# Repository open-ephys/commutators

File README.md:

> [!Important]  
> This repository has been split into dedicated repositories for each design:
>
>  - https://github.com/open-ephys/commutator-coax
>  - https://github.com/open-ephys/commutator-spi
>  - https://github.com/open-ephys/commutator-dual
>  - etc.
>
> Future commutator designs, issue tracking, etc. will take place in those repositories.
> This repository is deprecated.

# Torque-free commutators for orientation-aware headstages and miniscopes
The wide-spread availability of 6 degree of freedom pose tracking using
internal-measurement units (IMUs) allows continuous monitoring of an animal's
rotational state in an environment. This obviates the need for tether torque
measurements to drive an active commutator since the rotational state of the
animal is known in real-time, and the commutator can simply follow along. This
permits the use of extremely thin [coaxial
tethers](http://www.axon-cable.com/en/02_products/06_coaxial-cables/02/index.aspx)
that cannot function with a standard active commutator because they are too
flexible to translate rotational torque.

This commutator functions with headstages and miniscopes that provide
provide appropriate rotational tracking information. Currently
supported devices are next-generation, serialized headstages and miniscopes
such as [ONIX headstages](https://open-ephys.github.io/onix-docs/index.html), 
and UCLA Miniscope 4.0, and Open Ephys 3D low-profile SPI headstages.
However, this device operations completely independently from the headstage
itself, so can be used with any device that provides accurate, drift-free
rotational state. It can even be used without an IMU, e.g. using video-based
rotation tracking since its remote control interface is agnostic to how
rotational measurements are taken.

## Features
- Variants for high bandwidth RF links up to 18 GHz and low-bandwidth SPI cables
- Optical table & 80/20 rail mountable
- Remote control using JSON-encoded commands
- Manual control using capacitive sense buttons
- Indication LED
    - Can be completely turned off
- Advanced stepper driver (TMC2130)
    - Voltage-controlled for silent operation
    - Precise motion using step interpolation (256 uSteps/step)
- USB powered and controlled
    - Internal super-capacitor circuitry prevents loading the USB bus during
      motion

## Usage

**Note**: A high-quality, within-spec micro USB cable must be used when connecting 
the commutator to the host computer.

### LED
The LED tells you about the commutator state:

1. Flashing red (*Charging*): commutator is charging internal super-capacitors.
   All controls and motor operation are locked. Wait until this process
   completes to use the device. It can take up to 30 seconds.
1. Solid red (*Disabled*): commutator is disabled. Motor is turned off and will not
   turn or respond to button presses or external commands.
1. Green (*Enabled*): commutator is enabled and permits both remote and manual
   (button) turn control. Buttons take precedence over remote commands.

### Buttons
The front panel has four buttons.

- __Enable/Disable__: toggle commutator enable/disable.
    - *Disabled* (LED is red): All motor output will halt instantly, and motor
      driver is powered down. Pressing directional buttons in the stopped state
      will not work. All target turns provided via remote calls will be
      cleared, such that re-enable the motor will not result in the commutator
      re-engaging an old target position. In this state, pressing 
      the Enable/Disable button, or sending the approriate remote
      command, will enable the device.
    - *Enabled* (LED  green): When in the *enabled* state, the LED will be
      green and the motor can be turned via button presses or RPCs . In this
      state, pressing the Stop/Go button, or sending the approriate remote
      command, will instantly disable the device.

- __Directional__ (2x): Manually control the motor rotation in the
  direction indicated on each button when the commutator is *Enabled*. These
  inputs take precedence over and override ongoing remote motor control.  When
  pressed, all target turns provided via remote control will be cleared, such
  that releasing them will not result in the commutator re-engaging an old
  target position. Remote commands sent when a button is being pressed are
  ignored.

- __LED__: pressing the LED will toggled on and off (e.g for cases where it presents an
  unwanted visual stimulus).

### Remote control interface
When manual buttons are not being pressed, the commutator accepts JSON-encoded
commands over its serial interface. Here are examples of all commands that can
be sent:
```
{enable : true}     // Enable commutator (default = false)
{led : false}       // Turn off RGB LED (default = true)
{speed : 250}       // Set turn speed to 250 RPM (default = 50 RPM, valid ∈ (0, 500] RPM)
{turn : 1.1}        // 1.1 turns CW
{turn : -1.1}       // 1.1 turns CCW

// Example multi-command. Any combo can be used.
// In this case:
// 1. Turn LED off
// 1. Set speed to 25 RPM
// 2. Excecute 1.1 turns CC
// Ordering of commands does not matter, it is determined by the firmware
{led: false, speed: 25, turn : -1.1}
```
The communator state can be read using the `{print:}` command  which will
return a JSON object containing version, state, and motor parameters.

### Saving settings
All control and speed parameters, whether changed via the remote or manual
interface, are saved in non-volatile memory each time they are changed. The
device will start in the same state it was last used.

## Firmware
The controller firmware is located [here](./firmware/commutator). It runs on a
[Teensy lc](https://www.pjrc.com/store/teensylc.html). To compile
this firmware and program the microcontroller, you need the following
dependencies:

- [Arduino IDE](https://www.arduino.cc/en/Main/Software)
- [Teensyduino add-on](https://www.pjrc.com/teensy/td_download.html)
- [AccelStepper](https://www.airspayce.com/mikem/arduino/AccelStepper/)
- [Arduino JSON](https://arduinojson.org/)

The firmware can be uploaded to the device using the [Arduino
IDE](https://www.arduino.cc/en/Main/Software). _Note that you will need to add
the [Teensyduino add-on](https://www.pjrc.com/teensy/teensyduino.html) to to
the Arduino IDE to program the Teensy_. When installing Teensyduino, you should
opt to install all of the bundled libraries as well. This takes care of
installing `AccelStepper` library rather than having to install it manually.
ArduinoJSON can be installed through the Arduino IDE's package manager.

## Construction

### Bill of Materials
The BOM is located [here](https://docs.google.com/spreadsheets/d/1M2R0Q2-OuRHzctt05BxtA3hxNcCHtRZHORzCKElmG1Q/edit#gid=1283420334).

### Mechanical
The mechanical component of the commutator are as follows:

1. RF Rotary Joint
1. 2x reduction gears (3D-printed)
1. NEMA-11 Stepper Motor
1. Housing (3D-printed)
1. Some fasteners

Mechanical designs are located [here](./mechanical/). STL files for 3D printing
are located in the `stl` subdirectory. Links to purchase each of these
components, including 3D-printed parts, can be found on the BOM.

### Electronics
The board used to control the commutator consists of the following elements:

1. [Teensy LC](https://www.pjrc.com/store/teensylc.html) for receiving
   commands and controlling all circuit elements.
1. [TMC2130 stepper driver](https://www.analog.com/media/en/technical-documentation/data-sheets/TMC2130_datasheet_rev1.15.pdf) for driving the
   motor.
1. Super-capacitor charge system and step-up regulator for providing
   high-current capacity drive to the motor driver directly from USB.
1. RGB indicator LED.
1. Capacitive touch sensors on the back side of the PCB that serve as buttons
   for manual commutator control

Board designs and manufacturing files are located [here](./pcb/). 

## Hardware License
This license pertains to documents in the `control-board`, `mechanical`, and
`resources` subdirectory.

This work is licensed to Jonathan P. Newman and Jakob Voigts under CC BY-NC-SA
4.0. To view a copy of this license, visit
https://creativecommons.org/licenses/by-nc-sa/4.0

The creation of commercial products using the hardware documentation in this
repository is not permitted without an explicit, supplementary agreement
between the Licensor and the Licensee. Please get in touch if you are
interested in commercially distributing this tool.

## Software/Firmware License
This license pertains to documents in the source code in the `firmware`
subdirectory.

Copyright Jonathan P. Newman

Permission is hereby granted, free of charge, to any person obtaining a copy of
this software and associated documentation files (the "Software"), to deal in
the Software without restriction, including without limitation the rights to
use, copy, modify, merge, publish, distribute, sublicense, and/or sell copies
of the Software, and to permit persons to whom the Software is furnished to do
so, subject to the following conditions:

The above copyright notice and this permission notice shall be included in all
copies or substantial portions of the Software.

THE SOFTWARE IS PROVIDED "AS IS", WITHOUT WARRANTY OF ANY KIND, EXPRESS OR
IMPLIED, INCLUDING BUT NOT LIMITED TO THE WARRANTIES OF MERCHANTABILITY,
FITNESS FOR A PARTICULAR PURPOSE AND NONINFRINGEMENT. IN NO EVENT SHALL THE
AUTHORS OR COPYRIGHT HOLDERS BE LIABLE FOR ANY CLAIM, DAMAGES OR OTHER
LIABILITY, WHETHER IN AN ACTION OF CONTRACT, TORT OR OTHERWISE, ARISING FROM,
OUT OF OR IN CONNECTION WITH THE SOFTWARE OR THE USE OR OTHER DEALINGS IN THE
SOFTWARE.

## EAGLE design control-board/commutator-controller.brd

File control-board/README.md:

## Commutator Control Board
This board is used to control the commutator's stepper motor.

1. [Teensy LC](https://www.pjrc.com/teensy/teensyLC.html) for receiving commands and controlling all circuit elements.
2. [TMC2130 Silent Stepper Stick](https://www.watterott.com/en/SilentStepStick-TMC2130) for driving the motor.
3. Super-capacitor charge system and step-up regulator for providing
   high-current capacity drive to the motor driver directly from USB.
4. RGB indicator LED.

### Usage

#### LED
The LED tells you about the commutator state

    1. Flashing red: commutator is charging internal super-capacitors.
       Wait until it stops flashing to use.
    1. Solid red: commutator in *stop* state. Motor will not turn.
    1. Green: external and manual control
    1. Pink: manual control only

#### Buttons
The front panel has four buttons.

- Stop/Go: toggle commutator enable/disable. When in the *stop* state, the LED
  will turn red and all motor output will halt. Pressing directional buttons in
  the stopped state will not work. When in the *go* state, the LED will be
  green or pink depending on operation mode and the motor can be turned.
- Directional buttons (2x): Manual control over the motors rotation in the
  direction indicated on each button when the commutator is the *go* state.
  These inputs override any other form of motor control.
- Mode Button: Pressing the LED toggles the operation mode (external or
  manual).  Holding the LED for 1 second will toggle it on and off.

#### Remote Control Interface
The commutator communicates over its serial interface using JSON. Here are
examples of all commands:
```

{enable : true}     // Enable commutator
{led_on : false}    // Turn off RGB LED
{mode : 1}          // 0 = manual, 1 = automatic (respond to turn command below)
{speed : 2.5}       // Scale base speed (100 RPM) by 2.5
{turn : 1.1}        // 1.1 turns CW
{turn : -1.1}       // 1.1 turns CCW

// Multi command
{mode: 1, speed: 2.5, turn : -1.1} // 1.1 turns CCW
```

### Firmware
Firmware is located [here](../firmware).

### Bill of Materials
The BOM is located [here](https://docs.google.com/spreadsheets/d/1M2R0Q2-OuRHzctt05BxtA3hxNcCHtRZHORzCKElmG1Q/edit?usp=sharing).

### Board Design Files
- `*.sch`: EAGLE schematic file
- `*.brd`: EAGLE board file
- `gerber/*.GKO`: board outline
- `gerber/*.GTS`: top solder mask
- `gerber/*.GBS`: bottom solder mask
- `gerber/*.GTO`: top silk screen
- `gerber/*.GBO`: bottom silk screen
- `gerber/*.GTL`: top copper
- `gerber/*.G2L`: inner layer 2 copper
- `gerber/*.G3L`: inner layer 3 copper
- `gerber/*.GBL`: bottom copper
- `gerber/*.XLN`: drill hits and sizes
- `stencil/*.CST`: solder stencil cutouts

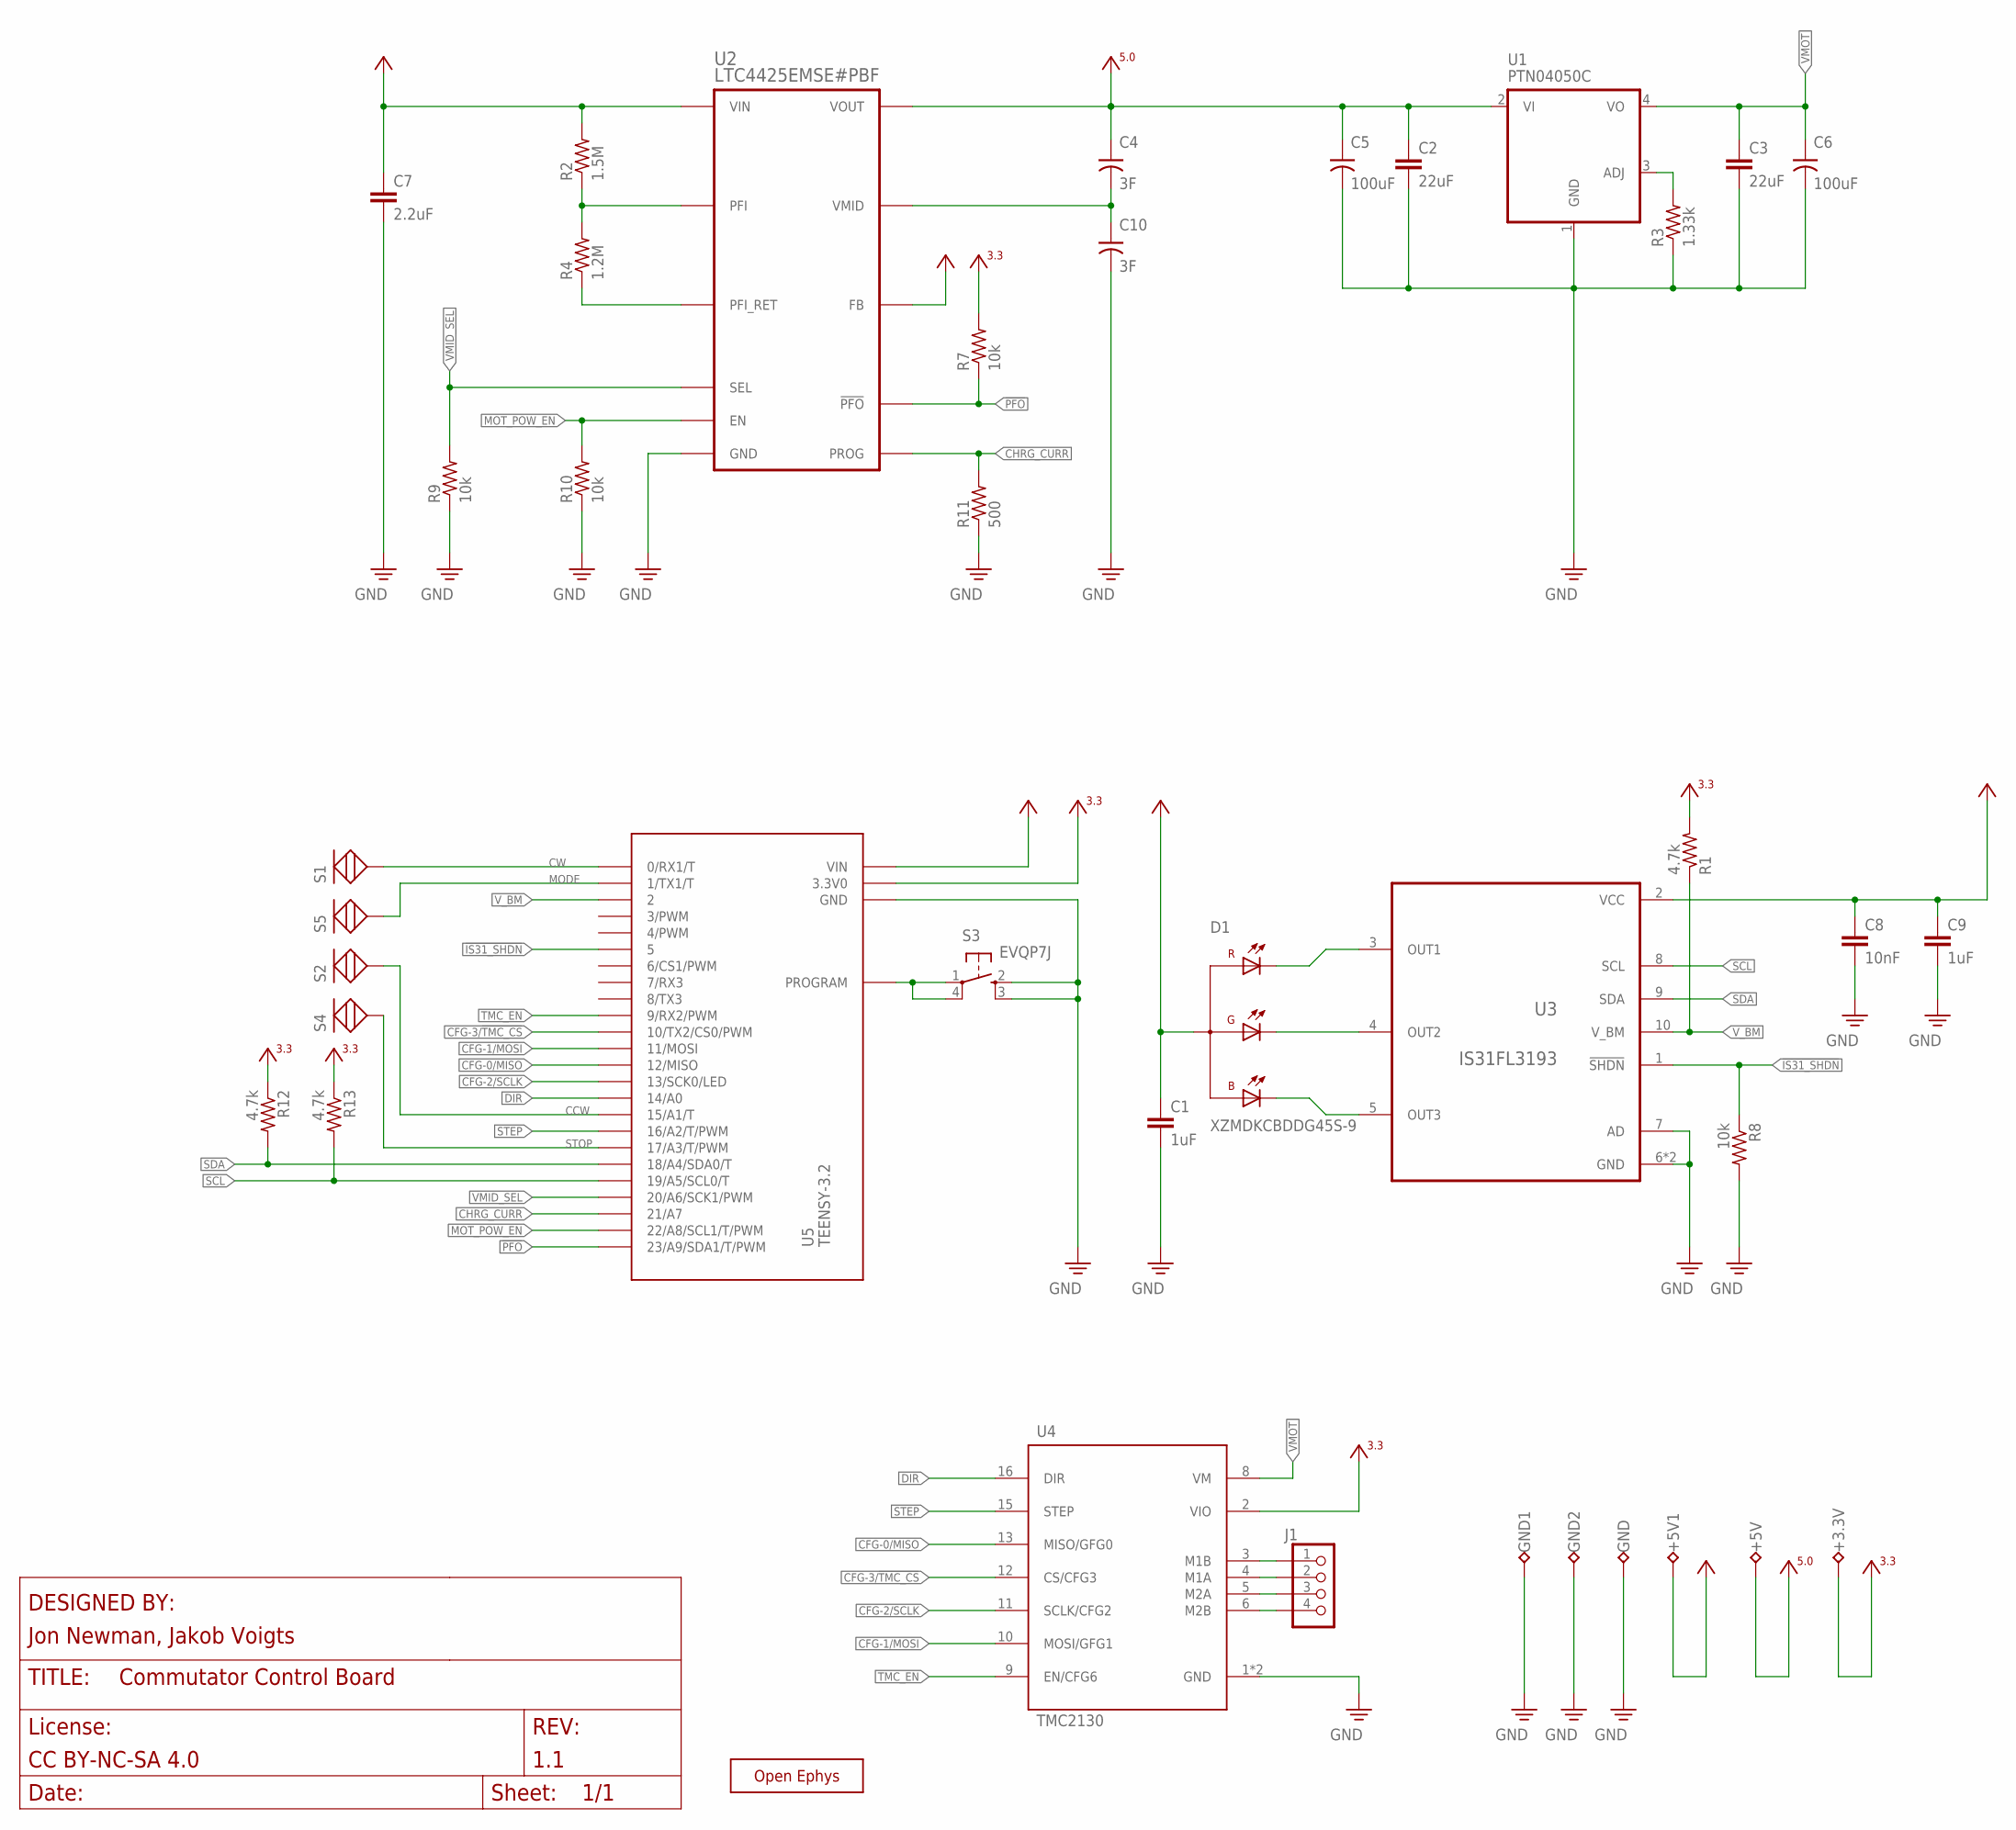
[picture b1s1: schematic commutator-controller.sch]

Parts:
+3.3V, +5V, +5V1: TPB2,54; B2,54
C1, C9: 1uF; 0603
C2, C3: 22uF; 1206
C4, C10: 3F; 1210-POL
C5, C6: 100uF; 153CLV-0807
C7: 2.2uF; 0805
C8: 10nF; 0603
D1: XZMDKCBDDG45S-9; PLCC-INVERTED-NOHOLE
GND, GND1, GND2: TPB2,54; B2,54
J1: PINHD-1X4_SMD-0.1"; JP4_SMD
R1, R12, R13: 4.7k; 0603
R2: 1.5M; 0603
R3: 1.33k; 0603
R4: 1.2M; 0603
R7, R8, R9, R10: 10k; 0603
R11: 500; 0603
S1, S2, S4, S5: TOUCH_1MM; TOUCH-1MM
S3: EVQP7J; EVQP7
U1: PTN04050C; PDSS-B4-MODULE
U2: LTC4425EMSE#PBF; MSOP-12-PAD
U3: IS31FL3193; PWSON-N10-3X3
U4: TMC2130; SILENT-STEPPER-STICK-SMD
U5: TEENSY-3.2; TEENSY_LC_SMD
X1: OE-LOGO_7X5; OE-LOGO-7X5

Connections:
!IS31_SHDN: R8.1, U3.1 (!SHDN), U5.5
!PFO: R7.1, U2.8 (!PFO), U5.23 (23/A9/SDA1/T/PWM)
+3V3: +3.3V.TP, R1.2, R7.2, R12.1, R13.1, U4.2 (VIO), U5.3.3 (3.3V0), U5.3V3 (3.3V0)
+5V0: +5V.TP, C2.1, C4.+, C5.+, U1.2 (VI), U2.1 (VOUT), U2.2 (VOUT)
CCW: S2.PAD, U5.15 (15/A1/T)
CFG-0/MISO: U4.13 (MISO/GFG0), U5.12 (12/MISO)
CFG-1/MOSI: U4.10 (MOSI/GFG1), U5.11 (11/MOSI)
CFG-2/SCLK: U4.11 (SCLK/CFG2), U5.13 (13/SCK0/LED)
CFG-3/!TMC_CS: U4.12 (CS/CFG3), U5.10 (10/TX2/CS0/PWM)
CHRG_CURR: R11.2, U2.3 (PROG), U5.21 (21/A7)
CW: S1.PAD, U5.0 (0/RX1/T)
DIR: U4.16 (DIR), U5.14 (14/A0)
GND: C1.2, C2.2, C3.2, C5.-, C6.-, C7.2, C8.2, C9.2, C10.-, GND.TP, GND1.TP, GND2.TP, R3.1, R8.2, R9.1, R10.1, R11.1, S3.2 (S), S3.3 (S1), U1.1 (GND), U2.PAD (GND), U3.6 (GND), U3.7 (AD), U3.PAD (GND), U4.1 (GND), U4.7 (GND), U5.GND, U5.GND1 (GND), U5.GND2 (GND)
MODE: S5.PAD, U5.1 (1/TX1/T)
MOT_POW_EN: R10.2, U2.6 (EN), U5.22 (22/A8/SCL1/T/PWM)
unnamed: R4.1, U2.7 (PFI_RET)
unnamed: R2.1, R4.2, U2.9 (PFI)
unnamed: D1.1 (CR), U3.3 (OUT1)
unnamed: J1.1, U4.3 (M1B)
unnamed: J1.2, U4.4 (M1A)
unnamed: J1.3, U4.5 (M2A)
unnamed: J1.4, U4.6 (M2B)
unnamed: R3.2, U1.3 (ADJ)
unnamed: D1.4 (CG), U3.4 (OUT2)
unnamed: C4.-, C10.+, U2.10 (VMID)
unnamed: D1.3 (CB), U3.5 (OUT3)
PROGRAM: S3.1, S3.4 (P1), U5.PROGRAM
SCL: R13.2, U3.8 (SCL), U5.19 (19/A5/SCL0/T)
SDA: R12.2, U3.9 (SDA), U5.18 (18/A4/SDA0/T)
STEP: U4.15 (STEP), U5.16 (16/A2/T/PWM)
STOP: S4.PAD, U5.17 (17/A3/T/PWM)
TMC_EN: U4.9 (EN/CFG6), U5.9 (9/RX2/PWM)
VCC: +5V1.TP, C1.1, C7.1, C8.1, C9.1, D1.2 (A), R2.2, U2.5 (FB), U2.11 (VIN), U2.12 (VIN), U3.2 (VCC), U5.VIN
VMID_SEL: R9.2, U2.4 (SEL), U5.20 (20/A6/SCK1/PWM)
VMOT: C3.1, C6.+, U1.4 (VO), U4.8 (VM)
V_BM: R1.1, U3.10 (V_BM), U5.2

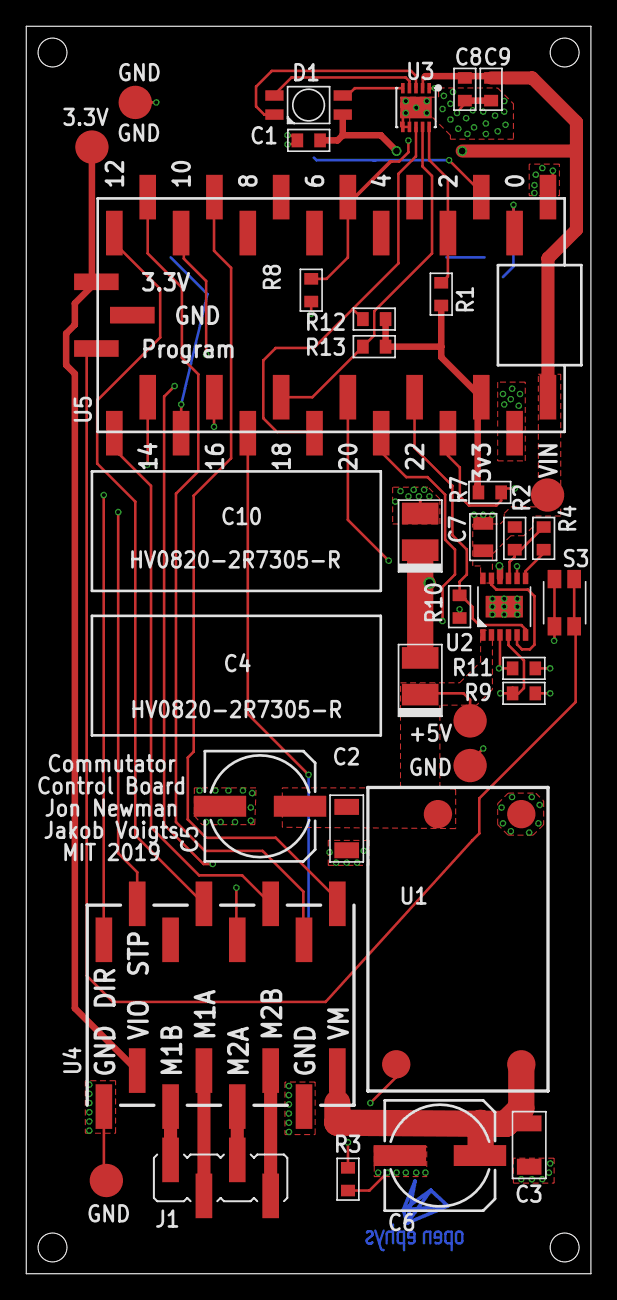
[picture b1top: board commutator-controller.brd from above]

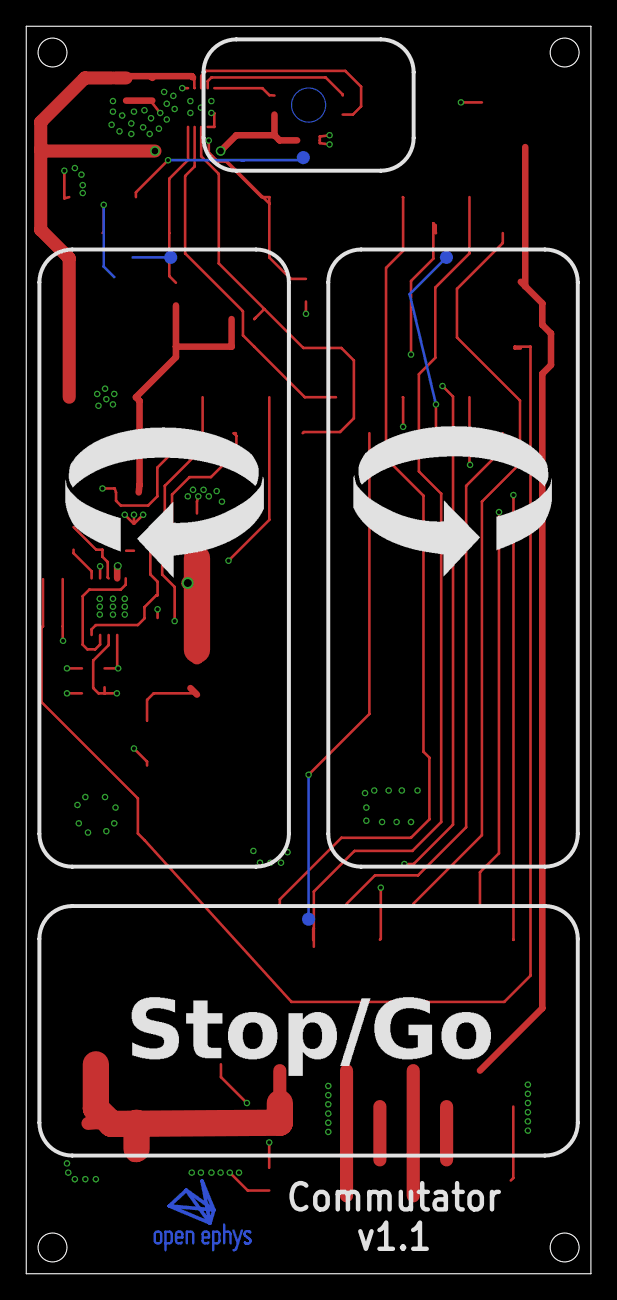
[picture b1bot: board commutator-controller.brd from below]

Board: 4 copper layers, 43.0 x 95.0 mm, 40 parts (5 on the bottom side), 36 nets.

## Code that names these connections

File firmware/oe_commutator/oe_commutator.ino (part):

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#define MOT_CFG6_EN         9

// Power options
#define MOT_POW_EN          22
#define VMID_SEL            20
#define CHARGE_CURR         21
#define nPOW_FAIL           23
#define CHARGE_CURR_THRESH  20 // Charge level required to allow operation. Arbitrary units
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
// RGB Driver
#define IS31_ADDR           0x68
#define IS31_SHDN           5
#define IS31_BM             2

// TMC2130 registers
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    Wire.setDefaultTimeout(200000); // 200ms

    // Enable LED current driver
    pinMode(IS31_SHDN, OUTPUT);
    digitalWriteFast(IS31_SHDN, HIGH);
    delay(1);

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    Wire.endTransmission();

    // Turn on the motor power
    pinMode(MOT_POW_EN, OUTPUT);
    digitalWriteFast(MOT_POW_EN, HIGH);
    delay(100);

    pinMode(VMID_SEL, OUTPUT);
    digitalWriteFast(VMID_SEL, HIGH); // 2.7V across each super cap

    pinMode(nPOW_FAIL, INPUT);
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
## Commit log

2018-12-17 initial commit 3d layout
2018-12-17 tweaked mounting
2018-12-18 updated commuttaor to use flanged rotary joint
2018-12-18 added pcb sizing info
2018-12-19 updated various parts
2019-01-07 Progress on commutator control board
    - Schematic is about complete with the exception of digital signal
    wiring, which should be done interactively to detangle wires
    - Added datasheets
    - Basic component placement
2019-01-07 Made housing 95mm tall to fit PCB
2019-01-09 Nearly complete control board
    - Silkscreen still needs work: button labels, device label, etc
2019-01-09 Completed control board
    - Pending review from jvoigts
2019-01-09 Small updates to control-board after review
    - Made sense of rotation direction icons less ambiguous and swapped
    positions
    - Moved push button back a bit
    - Remove copper layer between LED and top side of board
2019-01-10 Added stop/go button to control board
    - Added README
2019-01-10 Added fourth mode button on control board
    - Sits around RGB LED window
    - Also, increased min via drill size to 0.3mm which greatly decreases
    board cost
2019-01-10 Updated housing and gears - Added cutouts for teensy and reset switch - Made PCB housing deeper - Fixed mounting screw features - Added keyed features to gears - Reduced rotary joint gear ID to match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
2019-01-31 Adjusted id of larger gear to better fit commutator
2019-02-01 Commutator firmware
    - RPC interface
    - Manual, touch sensor interface
    - LED control
    - Saves settings
    - Etc, etc.
2019-02-01 Firmware updates and repo cleanup
    - Firware updates: manual, remote, and both control states now
    - Made all parameter values output referenced (to take care of 2x gear
    reduction)
    - Moved mechanical stuff to mechanical folder
2019-02-01 Added lincenses
    - Hardware is OHL v1.2
    - Software is beerware
2019-02-02 Updates to README, firmware, and control-board
    - Fixed mirrored pads for super capacitor charger
    - Switched Teensy LC for Teensy 3.2
    - Moved Teensy in 2mm so that housing does not need large cutout, but
    small one for micro USB
    - Fixed other small issues with the circuit
    - Some small changed to firmware: speed now provided directly in RPM
2019-02-02 Moved license to top level directory
2019-02-02 Update README.md
    Fix broken links.
2019-02-04 Tweaks to commutator housing - Made pcb compartment in housing deeper - Added extra height to bottom part so it can stand on surface
2019-02-14 Minor README update.
2019-06-02 Fixed firmware
    - Manual buttons work during remote turning
    - Stop button is immediate
2019-06-25 updated gear to fit the spinner RF joint
2019-09-13 Fix charging bug in firmware
    - The controller appeared to be unresponsive because it was not
    reporting when it was charging the supercaps. This commit fixes that
    - Also, I now turn off the controller 0.5 sec after the target turn has
    gone to 0. This may be a bad idea due to error accumulation.
    - Update the schematic of controller and provide new pdf
2019-09-22 Update gear_b.stl to match the current part
    - Fits the German rf rotary joint
2019-12-12 added dual channel doc
2019-12-23 Updates to README to get it ready for public release
    - Added licenses for hardware and software designs
    - Fully updated the BOM on google sheets and put links to in README
    - Update README to match the current firmware operation
2019-12-23 WIP 2 channel commutator
2019-12-24 initial design of dual-channel commutator housing
2020-01-17 Mechanical updates and added STLs
2020-09-22 Update README
    - Also move the CC BY-SA-NC 4.0 license for hardware
    - Add instructions for using {print:} command
    - Removed obsolete documentation
2020-09-22 Properly configure StealthChop mode for TMC2130
    - It was not actually on before
    - Also configure required control registers for this particular circuit
    (external current sense resistor, max run and hold current, max PWM
    characteristics, etc)
2020-09-26 Improvements in commutator firmware
    - When motor is stopped, driver is inactivated making the axle easy to
    turn
    - When motor is active but stopped, the driver continues to supplies a
    small amount of holding current so that error is not accumulated from
    repeated activation/inactivation of motor driver during stopped
    - The motor passively stops when a manual turn button is released to
2020-09-26 Small changes to the commutator driver board
    - No change in BOM or functionality
    - Added silkscreen outline to LED touch pad
    - Added OE logo
    - Remove license from silkscreen
2021-04-22 Small fixes to control board for production
    - Vias under LED driver were not symmetrical which caused delta-T during
    reflow and therefore bad settling of device. I made them symmetrical
    - Removed a couple random copper lines
2022-05-10 Update README.md
    - Fix BOM link
2022-10-17 Update README.md
    Add note about USB cable requirements to README
2023-03-20 Add mechanical design for 4 channels commutator
2023-03-20 Remove useless copies of dual chan
    Used as template to make the quad version. Not needed anymore
2023-03-20 Create readme.md
    Add readme to credit making lab and warn about potential issues
2023-03-24 add SPI enclosure prototype CAD files
2023-04-04 jon revisions + enclosed motor
2023-04-04 stl/step files for producing gears
2023-04-05 rev3
2023-04-05 added clearance for gear
2023-04-10 45 deg bevelled gear
2023-04-12 embiggened gears
2023-04-12 update production files
2023-07-17 jon's changes
    fillets added. I think this version was printed and sent
2023-07-19 production files updated to the ones printed by shapeways, source files not in sync
2023-09-11 createad notch for power button per production team's request
2023-09-14 widened m2.5 clearance holes for mounting nema stepper motor (2.7mm->3mm)
2023-10-25 Fix race condition resulting incorrect motor target
    - There was an issue with commands issued in quick succession, combined
    with the ability of the motor turn ISR to reset the target position to 0
    that caused steps to be lost in certain circumstances
    - The ISR has been minimized and now does not manipulate state outside
    of the motor object
    - target_turns is now never reset except when it is about to overflow
2023-11-06 Firmware version 1.3.0
    - Make threshold for button presses a function of their measured
    capacitance.
    - Turn off motor driver during initial supercap charging
    - Add diagnostic info to {print:}
2023-11-08 Fix gear ratio for dual coax commutator
    - Also reduced required capacitance change required to detect a button
    press
2023-11-16 Firmware version 1.4.0
    - Simplified button press logic following issues at SfN
2023-11-21 Control board rev. C
    - Move to KiCAD
    - Replace silent stepper stick with on-board circuit
2023-12-06 Board revision C
    - Sent to JLCPCB for testing
2023-12-19 Overhault button touch algorithm
    - Switch algorithm to differentiations -> integration method to drop
    intial capacitance of each button
    - Additionally, we do not take multiple readings and average but form an
    average over multiple calls to check the button capacitance, which
    results in much snappier interaciton with the panel
2024-01-23 Increase R_prog to 2.49k
    - This accounts for overhead current drawn from VCC by the Teensy and
    LED driver
2024-01-23 Add pdf of latest schematic
2024-01-24 Add teensy-type dependent filter for touch integration function
    - Touch sensor algorithm now filters capacitive deltas
    - Teensy 3.2 and Teensy LC have different capactive noise levels. A
    macro was added to dictate what teensy is being used and therefore
    what threshold to use for integrating capactive deltas
2024-05-01 Fix nan issue
    - When {turn:nan} was sent to the commutator it would completely freak
    out. We now filter for this situation.
2024-09-19 Update dual channel commutator enclosure
    - Enclose motor
    - Improve PCB mounting
    - Remove large hole that exposed Teensy
2024-09-26 Rev D Schematic
    - split schematic into several pages
    - replace teensy with rp2040
    - Add dedicated capacititave touch sensor ic
    - Replacec Micro-Usb with USB-C
2024-09-26 Remove redundant file
2024-09-26 Replaced through-hole components with SMD
    - Other small edits (e.g. optional jumper to force USB-boot)
2024-09-26 Add GPIO to programming header
2024-09-26 Initial Rev D PCB component layout
    - This is the initial component layout
    - Some traces are routed, but a review seems wise before I grind
    out routing the rest of the traces and start resolving DRC
2024-09-26 Move stickers, silkscreen label, & header
    - They were interfering in the previous commit
2024-09-27 Rev D PCB WIP for Review
    - Before going into further minutiae, get review
    - Components are laid out and routed
    - Fails DRC check, requires vias for better GND plane, there are traces
    in the outer keepout zone, remove S5?
2024-09-27 Revision D of controller PCB
    - Small changes during PCB review
    - This commit will be fabricated
2025-09-05 Update README.md
    - Add deprecation notice

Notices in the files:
control-board/commutator-controller.sch:
LICENSE: CC BY-NC-SA 4.0
